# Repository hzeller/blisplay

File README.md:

<h1 align="center">an Open Source Hardware tactile display for the blind.</h1>

## Seeing for the blind: make it tactile
Without optical sense there is another way of conveying spatial information
in an accessible way by providing a [tactile experience][tactile-graphic].
Usually, these are 'offline' methods by using swell papers or embossers to
generate a surface representing graphics.

I wanted to make a "display" that can provide such tactile surface directly from
the computer. Of course, it would be a huge effort (and pretty heavy) to build
a surface with tens of thousands of actuators to poke out little dots, so
instead let's just strap a small amount of actuated dots just covering the
fingertip under the finger and actuate them depending on where the finger is
in the image. A display for the blind, let's call it **blisplay**.

#### About this README

I have to apologize to visually impaired readers of this README as it
contains are a couple of pictures in here which make it less accessible.
But these hopefully help your sighted peers to get them started
building the device. To make up for it, there are some explanations that
might sound lengthy and detailed to sighted readers - these are part of the
proverbial thousand words describing the pictures.

#### Direct optical to tactile

There is a simple direct way to do it: mount a camera under the set of tactile
pixels, watching the optical image underneath, directly translating optical
to tactile information; while moving the finger over the surface, the image
underneath will be translated to tactile information, allowing the user to
experience the full image by following the lines on the surface. This is the
first implementation as it is straightforward.

So the first prototype is sitting on a stand-off to be able to watch the
surface underneath.

![Rendering of a fully assembled unit][img-render-oblique]  |
   ![Photo of prototype unit][img-photo-oblique]
-----------------------------------|-------------------------|
Blisplay assembly rendering        | Photo of the actual unit|

#### Display an image from a computer

Another way is to show a picture directly from a computer by having it watch
the position of the finger and present the pixels representing the current
covered area. There are various ways doing it, e.g. with a graphic tablet
encoding the absolute position. Or, these days, it should be easy with the
ubiquitous smart-phones: load an image on the phone and point its camera to
the surface the hand is moving over; with simple image processing, we can
follow the finger relative to the background and send the right tactile
pattern to the device.

### Design goal
The design goal of this project is to make it simple to build
by some technically inclined person for their blind peers.

Right now, I am working on hashing out the most practical way to do so. The
first prototype is already pretty simple, but some more simplification
needs to be done (in particular for the coil wiring, see below).

I would hope for build parties in the future in which hacker-spaces
build devices for their local blind community and improve on the design based
on the feedback.

### Status
The first prototype is assembled and shows desirable functionality and force
of the actuators. The ADNS-3050 chip used as camera is connected but has yet
to be debugged to get some reading of the frame; also the lens-assembly for
getting an image on the sensor has to be worked on.

The current device is a little bit bulky (about 45mmx90mm), but ideas lined-up
for a second prototype will reduce that. Current resolution is about 2mm in a
4x6 grid (8mm x 12mm). This is already pretty close to the spacial resolution of
finger-tips, but future iterations will hopefully improve that more.

### History
What motivated all this? I have a blind friend for whom I made tactile maps
by gluing thread on paper or transferring graphics using swell-paper
as well as other means to make graphical things accessible.
But in particular I wanted to directly provide images from a computer without
these detours.

In about 2006, I made the very first prototype of this project of a location
aware pixel actuator, [using a modified relay solenoid strapped to a pen of a
graphics tablet](./img/old-prototype-2006.jpg). The single pixels was not very
intuitive though as it requires a lot of scanning by finger. Fast forward do
2018, time to revisit this project and use 3D printing and hobbyist-affordable
PCB making that came up in the meantime to make this much more useful.

## Actuators

There are several ways we could think of actuating raising dots to get the
tactile experience. One of the most important constraints though will be size:
we need to have these pixels reasonably dense and a few of them to be able
to be useful. In the first prototype, these are 4x6 pixels in a 2mm grid
(somewhat diagonal grid as we see later). Also, ideally we can modulate the
force of the pixels to emulate different elevations.

The modulation constraint means that we can't use a bi-stable solenoid but
need to go with a moving coil or moving magnet approach.

The density constraint means that we need to optimize the use of the available
volume for the moving parts and keep supporting structure (magnets, wiring, ...)
out of the way.

### Moving coil
So let's just do the first and simplest thing that comes to mind: use a
conductor in a magnetic field, generating a [Lorentz force].
The conductor is made out of a PCB coil, essentially a square area with a
protruding bit on one side (the tactile dot) and a fulcrum in the
center other side.

#### Stack of flat coils in magnetic field
To visualize (sighted readers also see this in the images): Let's imagine
your left hand facing you with the thumb up.
The hand represents the flat coil with a conductor going across the index
finger towards your wrist, then down, and out again towards the pinkie.

The thumb is extended out and represents the little dot that will poke.
This coil/hand is hinged at the tip of the middle finger.
The magnetic field is going through the flat hand coming from the back of
your hand at the top and at the bottom into your hand pointing towards the back.

With a current through the conductor, the top conductor will move up and so will
the reversed bottom conductor through the reversed magnetic field. This coil
will hinge and move the thumb up and down.

With a stack of these coils, we can have a lot of actuators in a pretty dense
space. A stack of 12 coils are grouped in four stacks of three.
In each triplet, the first coil has the protruding dot the furthest away from
the fulcrum, the next 2mm in (as if the thumb was mounted more towards your
index finger), the next 4mm in.
That way, we can have three independently controlled pixels in that direction.
The coils are made of 0.4mm thick PCB, so the stack can be made 2mm thick with
some wiggle room to spare.
With four of these triplets, we have 4x3 pixels with a 2 mm distance between
adjacent pixels (but slightly diagonal due to the stacking).

In the following demonstration, the current direction is
shown in the traditional plus to minus direction to align with the common
Lorentz right-hand rule.

  ![Animation of forces in magnetic field][img-anim-lorentz] |
![A stack of three coils with offset fingers][img-triplet-coil] |
-----------------------------------------------|---------------------|
Moving coil in magnetic field. Red arrow: varying current; Blue: static magnetic field; Green: resulting force | A triplet of coils with offset dots, stacked.

If we hinge two stacks right and left with the poky bits meeting at the center
we have a 6x4 pixel arrangement.

![Rendering showing view of actuators without magnets][img-render-no-magnets] |
  ![Closeup of pixels in prototype][img-photo-pixels]
-----------------------------------------------|---------------------|
View of all actuator blade coils. Hinged at opposite ends of the assembly, they allow 6x4 pixels in the center.  | Closeup of pixels in prototype (here, only 22 pixels)

With each blade coil mounted, they can be individually controlled.

![Animation of pixels scanning and poking through finger-pad][img-anim-pixel-scan]

## Driving Circuit

The coils need to be driven in the low hundreds of milliampere; for this simple
transistor drivers are used (maybe in the future half-bridges ?).

The driving circuit for the coils are currently two identical boards with
a shift register and ULN2803 open collector driver chips. The two chained
boards are presenting itself as a 32 bit shift register to the microcontroller
and has two LEDs and allow to connect up to 30 coils. The
latch input is latching on the positive edge, so it can be used as an SPI
client.

The component choice was based on what I had lying around at home, but a
future iteration of this board will be more compact, e.g. by using
NCV7751 chips that contain 12 drivers and an SPI interface in one package
(or maybe TLE94112 with half-bridges).

 |
    
--------------------------------------|-----------------------------------|
15 Transistor serial driver board     |  ... for realz                    |

## Controlling Circuit
The controlling circuit right now is a simple ATTINY85 using SPI to
communicate with the driver circuit and the ADNS-3050. Two pins are used as
Chip Select for either the camera or the coil drivers.

This prototype is mounted on a raster board. The camera does not yet
have an optical lens assembly as the readout still needs to be debugged.

A future version will likely use a Microcontroller with more pins (ATTINY44) to
be able to also drive an additional 0.96" OLED display to help visualize while
debugging.

![Circuit from the bottom of the assembly][img-circuit]

# Building

Right now, the prototype design is still somewhat in flux, but you can already
build a prototype. Mail me directly if you have specific questions while doing
so.

### 3D printing and laser cutting

You need to have OpenSCAD installed, then, in the top-level directory, type

```
 make
```

This will generate the following files inside a `fab/` directory:

  * `print_yokes_magnetic_filament.stl` yokes to be printed with magnetic
    filament (I found that magnetic filament is actually not that good. I ended
    up printing them hollow and fill with iron powder. The next prototype will
    just use simple iron parts from the hardware store).
  * `print_yoke_spacers.stl` The spacers, to be printed with regular,
    non-magnetic filament.
  * `lasercut_sidewall.dxf` the side-wall to elevate the assembly to have a
    free view below. These dimensions are super rough right now and will change
    once there is a lens-assembly on the camera.
  * `finger_cradle.stl` is a hollow shape keeping the finger in place over
    the actuators. You might need to adapt parameters to your finger-diameter.
    (currently does not lock into the rest of the assembly, you might need
    some double-sided tape).
  * The `assembly_tool_spacer_holder.stl` is not technically part of the
    blisplay, but a useful tool holding the parts while assembling.
  * In the top-level directory, there is also a PostScript file `coil-shape.ps`
    describing the coil shape, which is converted to a DXF file by the
    Makefile. That is used for the PCBs, but are also imported in the OpenSCAD
    model. Don't worry about these, the generated DXF file is also checked in.
  * For the assembly I am [using magnets][magnet-used] of size
    38.1mm x 6.35mm x 6.35mm.

### Printed circuit boards
Right now, there are two printed circuit boards.

  * The driver boards. These are in the [`driver-pcb/`](./driver-pcb)
    directory. These are likely to change to be more compact. [You can order
    them from OshPark][oshpark-driver] (not affiliated).
  * The coils: In the directory [`coil-pcb/`](./coil-pcb), you find the program
    to generate the coil footprint and a simple KiCAD project putting the
    coil shape and the coil footprint together. Future versions will have a
    slightly different shape (wedge form) and different connecting pads.
    Unfortunately, OshPark does not do 0.4mm thick PCBs, so you have to use
    some other PCB service to make these.
  * There is no microcontroller board yet, right now this is on a raster
    board. Once the optics is figured out, this (and possibly together with
    different driver chips) will be part of the next iteration.

### Wiring up the coils
Wiring up the coils is the most time-consuming currently. The coil-PCBs have
solder points to solder wires to, but just soldering on even a 0.1mm thick
enameled wire already makes them too thick to work well in the assembly.

So in the first iteration, I scratched a tiny groove with a scalpel into the
PCB, then embedded the enameled wire into that grove and soldered it flat
into there. Then insulation covered that with transformer lacquer.
Future experiments certainly will attempt to make this less tedious, e.g.
hot-bar flexible PCB on top of the board instead.

The coil PCB has pokey-bits for all three positions; once the coil is ready to
mount, remove the unused ones with a side-cutter.

![The coil][coil-render] | ![Placing wire in groove][coil-groove]
--------------------------------------|-----------------------------------|
The coil PCB. Unused pokey bits are to be clipped off. Note the different lengths to accommodate the finger curvature. | Placing a wire in groove prepared with scalpel to keep wiring as flat as possible.

The wiring to the driver boards is currently via soldering, but that makes it
a pain to assemble and hard to maintain.
Thus future versions will use flat-flex connectors.

![finished coils][coil-finished]      | ![Wiring coils to driver][coil-attached]
--------------------------------------|-----------------------------------|
Finished coils, ready to mount.       | Wiring of coils to driver board.

### Code
The code is in the [`src/`](./src) sub-directory. Build with the makefile
there, then flash using an Atmel programmer via avrdude (`make flash`).

# License
Any PCBs and 3D printed parts are Open Source Hardware licensed
with `CC-BY-SA` license. Any code is licensed with the GPL v3.

[logo]: ./img/blisplay-logo-medium.png
[img-render-oblique]: ./img/prototype-rendering.png
[img-photo-oblique]: ./img/prototype-photo.jpg
[img-render-no-magnets]: ./img/prototype-actuators-no-magnets.png
[img-photo-pixels]: ./img/photo-actuator-pixels.jpg
[img-anim-lorentz]: ./img/coil-lorentz-anim.gif
[img-triplet-coil]: ./img/triplet-stack.png
[img-anim-pixel-scan]: ./img/scan-pixel-anim.gif
[img-circuit]: ./img/prototype-circuit-view.jpg
[magnet-used]: https://www.kjmagnetics.com/proddetail.asp?prod=BX844
[tactile-graphic]: https://en.wikipedia.org/wiki/Tactile_graphic
[Lorentz force]: https://en.wikipedia.org/wiki/Lorentz_force
[oshpark-driver]: https://oshpark.com/shared_projects/nWsVpTrj
[coil-groove]: ./img/solder-wire-in-groove.jpg
[coil-render]: ./img/coil-rendering.png
[coil-finished]: ./img/soldered-coils.jpg
[coil-attached]: ./img/coil-connect.jpg

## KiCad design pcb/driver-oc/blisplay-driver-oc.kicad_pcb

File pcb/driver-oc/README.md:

An open collector driver.

Distance Flat flex: 21mm

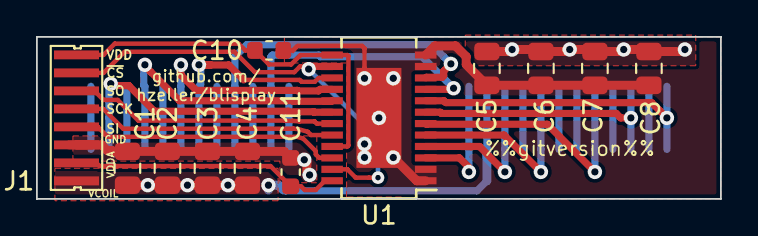
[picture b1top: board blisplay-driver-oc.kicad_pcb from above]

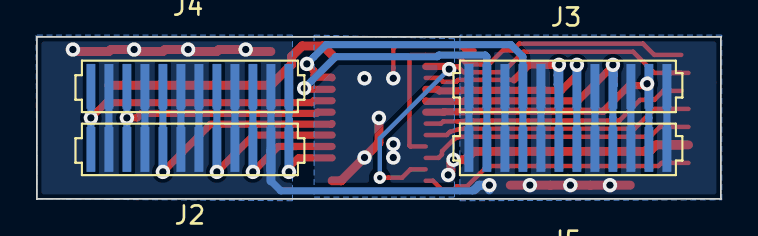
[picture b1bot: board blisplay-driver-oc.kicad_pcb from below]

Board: 2 copper layers, 38.0 x 9.0 mm, 16 parts (4 on the bottom side), 20 nets.

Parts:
C1, C2, C3, C4, C5, C6, C7, C8: 10μ; C_0805_2012Metric
C10, C11: 100n; C_0603_1608Metric
J1: Conn_01x08; driver-connect
J2, J3, J4, J5: Flex; flex-12
U1: NCV7751; SSOP-24EP_3.9x8.7mm_P0.635mm

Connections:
/Coil_1: J2.1, J4.1, U1.3
/Coil_2: J2.3, J4.3, U1.4
/Coil_3: J2.5, J4.5, U1.5
/Coil_4: J2.8, J4.8, U1.6
/Coil_5: J2.10, J4.10, U1.7
/Coil_6: J2.12, J4.12, U1.8
/Coil_7: J3.2, J5.2, U1.9
/Coil_8: J3.4, J5.4, U1.10
/Coil_9: J3.6, J5.6, U1.15
/Coil_10: J3.7, J5.7, U1.16
/Coil_11: J3.9, J5.9, U1.17
/Coil_12: J3.11, J5.11, U1.18
/SCK: J1.4, U1.20
/SI: J1.5, U1.22
/SO: J1.3, U1.19
/VCOIL: C1.1, C2.1, C3.1, C4.1, C5.1, C6.1, C7.1, C8.1, J1.8, J2.2, J2.4, J2.6, J2.7, J2.9, J2.11, J3.1, J3.3, J3.5, J3.8, J3.10, J3.12, J4.2, J4.4, J4.6, J4.7, J4.9, J4.11, J5.1, J5.3, J5.5, J5.8, J5.10, J5.12
/~CS: J1.2, U1.14, U1.23
GND: C1.2, C2.2, C3.2, C4.2, C5.2, C6.2, C7.2, C8.2, C10.2, C11.2, J1.6, U1.0, U1.1, U1.2, U1.11, U1.12
VDD: C10.1, J1.1, U1.13, U1.21
VDDA: C11.1, J1.7, U1.24

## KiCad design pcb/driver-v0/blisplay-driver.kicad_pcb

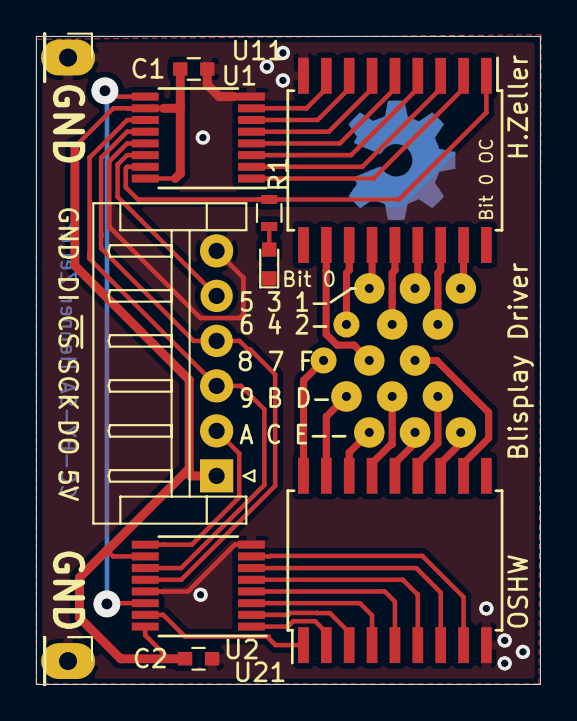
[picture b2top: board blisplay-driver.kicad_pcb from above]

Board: 2 copper layers, 28.0 x 36.0 mm, 16 parts (0 on the bottom side), 39 nets.

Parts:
C1, C2: C; C_0603
D1: LED; LED_0603
J1: Conn_01x06; JST_EH_S06B-EH_06x2.50mm_Angled
J2, J3, J4, J5, J6: Conn_01x03; Pin_Header_Straight_1x03_Pitch2.54mm
J7, J8: Conn_01x01; Pin_Header_Straight_1x01_Pitch2.54mm
R1: 1k; R_0603
U1, U2: 74HC595; TSSOP-16_4.4x5mm_Pitch0.65mm
U11, U21: ULN2803A; SOIC-18W_7.5x11.6mm_Pitch1.27mm

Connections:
+5V: C1.1, C2.1, J1.1, U1.10, U1.16, U2.10, U2.16
/Bit0: R1.1, U1.15, U11.1
/CS: J1.4, U1.12, U2.12
/MISO: J1.2, U2.9
/MOSI: J1.5, U1.14
/SCK: J1.3, U1.11, U2.11
/carry: U1.9, U2.14
GND: C1.2, C2.2, D1.1, J1.6, J7.1, J8.1, U1.8, U1.13, U2.8, U2.13, U11.9, U21.9
unnamed: D1.2, R1.2
unnamed: J2.1, U21.16
unnamed: J2.2, U21.14
unnamed: J2.3, U21.12
unnamed: J3.1, U21.17
unnamed: J3.2, U21.15
unnamed: J3.3, U21.13
unnamed: J4.1, U21.18
unnamed: J4.2, U11.11
unnamed: J4.3, U21.11
unnamed: J5.1, U11.12
unnamed: J5.2, U11.14
unnamed: J5.3, U11.16
unnamed: J6.1, U11.13
unnamed: J6.2, U11.15
unnamed: J6.3, U11.17
unnamed: U1.1, U11.2
unnamed: U1.2, U11.3
unnamed: U1.3, U11.4
unnamed: U1.4, U11.5
unnamed: U1.5, U11.6
unnamed: U1.6, U11.7
unnamed: U1.7, U11.8
unnamed: U2.1, U21.2
unnamed: U2.2, U21.3
unnamed: U2.3, U21.4
unnamed: U2.4, U21.5
unnamed: U2.5, U21.6
unnamed: U2.6, U21.7
unnamed: U2.7, U21.8
unnamed: U2.15, U21.1

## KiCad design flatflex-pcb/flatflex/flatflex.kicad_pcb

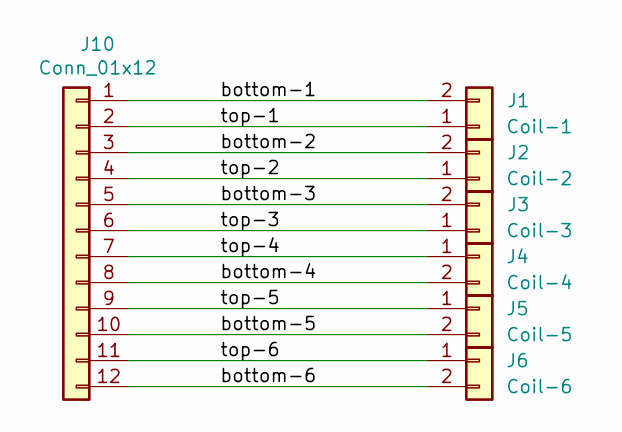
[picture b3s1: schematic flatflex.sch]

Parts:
J1: Coil-1; flex-coil-connect
J2: Coil-2; flex-coil-connect
J3: Coil-3; flex-coil-connect
J4: Coil-4; flex-coil-connect
J5: Coil-5; flex-coil-connect
J6: Coil-6; flex-coil-connect
J10: Conn_01x12; flex-12

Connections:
/bottom-1: J1.2, J10.1
/bottom-2: J2.2, J10.3
/bottom-3: J3.2, J10.5
/bottom-4: J4.2, J10.8
/bottom-5: J5.2, J10.10
/bottom-6: J6.2, J10.12
/top-1: J1.1, J10.2
/top-2: J2.1, J10.4
/top-3: J3.1, J10.6
/top-4: J4.1, J10.7
/top-5: J5.1, J10.9
/top-6: J6.1, J10.11

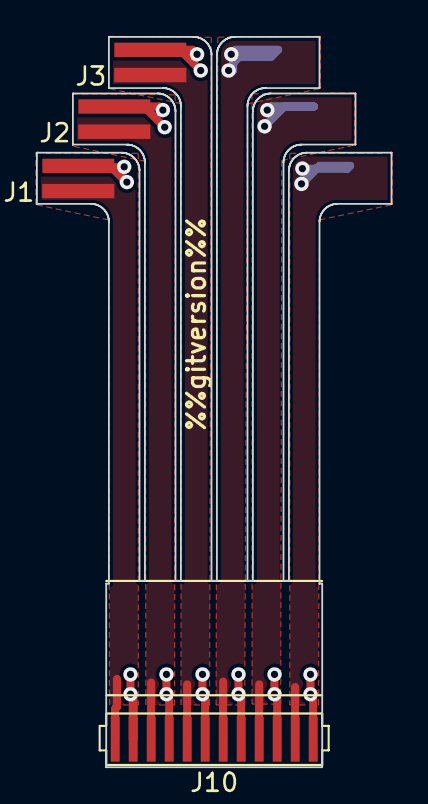
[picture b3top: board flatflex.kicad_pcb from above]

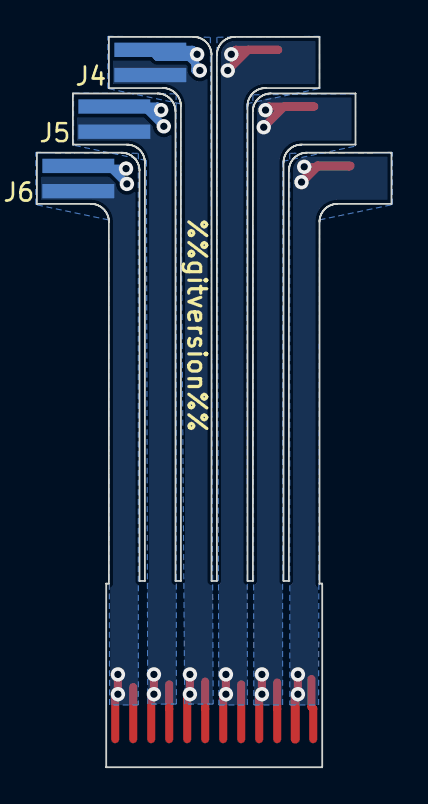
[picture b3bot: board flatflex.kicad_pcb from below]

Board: 2 copper layers, 19.7 x 40.6 mm, 7 parts (3 on the bottom side), 12 nets.

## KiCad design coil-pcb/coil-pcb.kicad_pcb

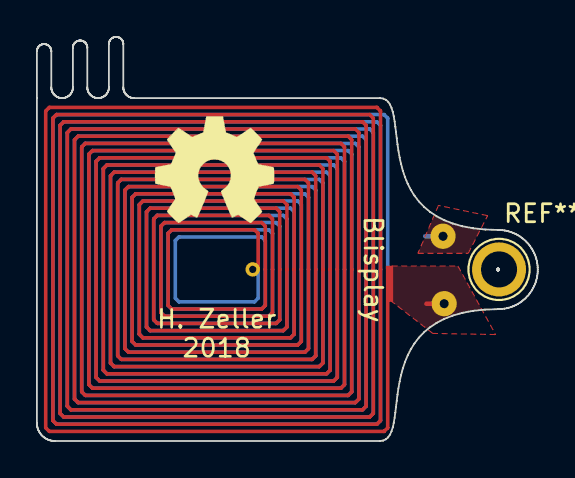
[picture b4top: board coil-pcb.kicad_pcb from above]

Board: 2 copper layers, 27.8 x 22.5 mm, 3 parts (0 on the bottom side), 2 nets.

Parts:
J1, J2: Conn_01x01; Pin_d0.7mm_L6.5mm_W1.8mm_FlatFork
L1: INDUCTOR; coil

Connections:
A: J1.1, L1.1
B: J2.1, L1.2

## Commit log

2014-02-19 Reactivate Blisplay project. Moving magnet will allow for faster reaction time and less 'clicking'; but also less force than solenoid.
2018-08-25 More compact coil packing by putting them all in the same homogenized magnetic field. Simplest of all actuators: just straight conductor in perpendicular field.
2018-08-25 Make coil shape more pleasing by using bezier curves (generate shape in PostScript, convert to DXF, then use in OpenSCAD).
2018-10-07 Coil PCB to be used inside Blisplay.
    o Programmatically generate KiCAD module for a two layer board
    coil.
    o Use DXF generated from PostScript as EdgeCuts outline for
    nice smooth shape (always making sure to have fillets in
    inner corners to be able to be manufuactured. DFM).
2018-10-21 First version of coil driver board.
2018-10-29 Make cut-out in lower yoke for driver PCBs.
2018-10-29 Parametrize yoke_spacer to include the dynamic width (which depends on the PCB).
2018-10-29 Add mounting holes to pull spacers solid in place.
2018-10-30 Add tool helpful for assembly. Provide a 'cover' for yoke.
    The yoke-cover is for the case it is printed hollow and filled with
    iron powder; then we need a lid to glue on.
2018-10-31 Add laser-cuttable side-walls.
2018-10-31 Add coil shape DXF, so that it does not need to be re-created on checkout.
2018-10-31 Automatically generate STLs and DXF via Makefile.
2018-10-31 some better names for printable modules.
2018-11-01 Write to coils via SPI.
2018-11-01 Better firmware name.
2018-11-01 Implemented ADNS3050 from datasheet. Nothing tested yet.
2018-11-04 Simulate actuators given an array of poxels.
2018-11-06 Make a basic logo: blisplay text with i-dot being intl. blind symbol
2018-11-06 Have a visualization angle of actuators for 'on' and 'off'
2018-11-06 Map coils to current wiring.
2018-11-06 gitignore some common generated files.
2018-11-06 Start README
2018-11-07 git ignore object files.
2018-11-07 First basic README with a couple of pictures.
2018-11-07 Add a finger-holder, replacing the flimsy finger-pad.
2018-11-07 Rename 'finger_holder' to better name 'finger_cradle'
2018-11-07 Have slightly shorter Pokey-Pins towards the center, matching finger curvature.
2018-11-07 Cleanup: move driver-PCB 3D shape used for illustration in scad file into driver-pcb/
2018-11-08 More coil-wiring pictures; improved picture captions.
2018-11-11 Smaller version, using steel from hardware store for yoke.
2018-11-15 Next step wiring: flat flex.
2018-11-17 Add some flat-flex connection rendering.
2018-11-17 Add some measurement annotations.
2019-01-04 fix typo
2019-05-27 Refine flatflex-outline. Make first experimental board out of it.
2019-05-27 Reorganize PCBs to be all in one sub-directory.
    Rename blisplay-driver to driver-v0 to not conflict with new
    drivers.
2019-05-27 Move coil-edge-cuts dxf in the coil/pcb directory.
2019-05-27 Make possible to read driver board with new KiCAD
    Not much effort to convert, as this is going to go anyway.
2019-05-27 Add a couple of README-stubs.
2019-05-27 Generally ignore *fab/ directories as they are generated.
2019-06-19 Adapt wiring to two-sided powering.
2019-06-19 Start driver-board to sit between the magnets.
2019-06-19 Add simple connector to driver board.
    This is not mirror symmetric which would be nicer for hassle-free
    wiring. Maybe there should be two variants.
2019-06-20 No pads zero needed for edge connect.
2019-06-20 Make assembly a little higher to accomodate new driver board size.
2019-06-21 Initial, fully routed version of open collector driver.
2019-06-21 Larger coils to accomodate driver PCB. Also: Remove obsolete modules.
2019-06-22 Label coil circuits. Pull EN to VDD.

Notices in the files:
pcb/driver-v0/blisplay-driver.kicad_pcb:
CC-BY-SA Henner Zeller
